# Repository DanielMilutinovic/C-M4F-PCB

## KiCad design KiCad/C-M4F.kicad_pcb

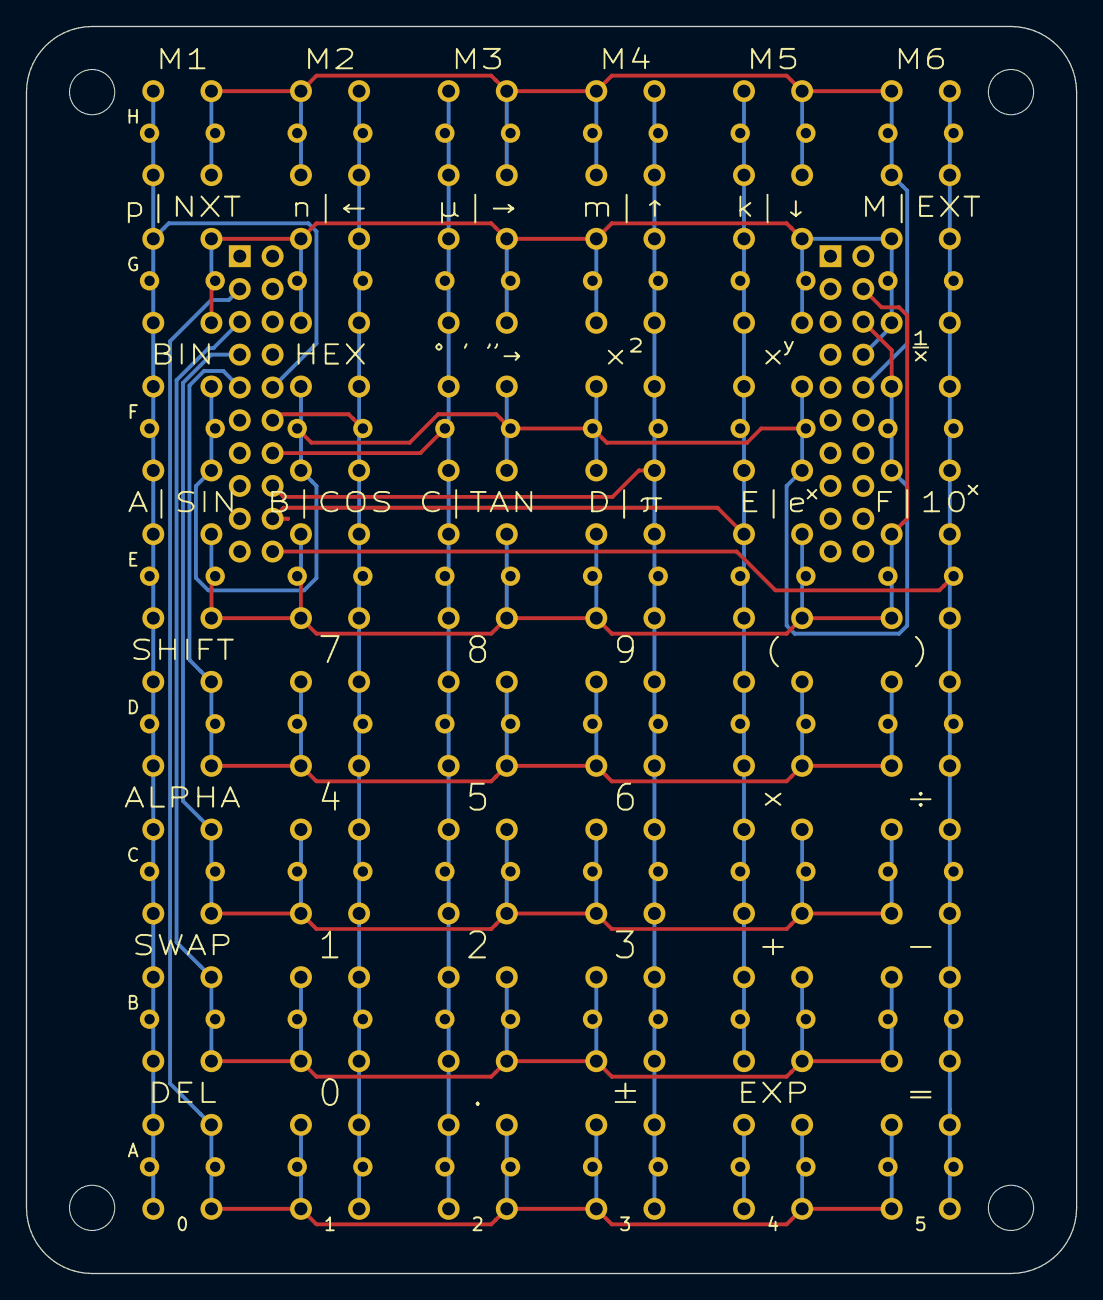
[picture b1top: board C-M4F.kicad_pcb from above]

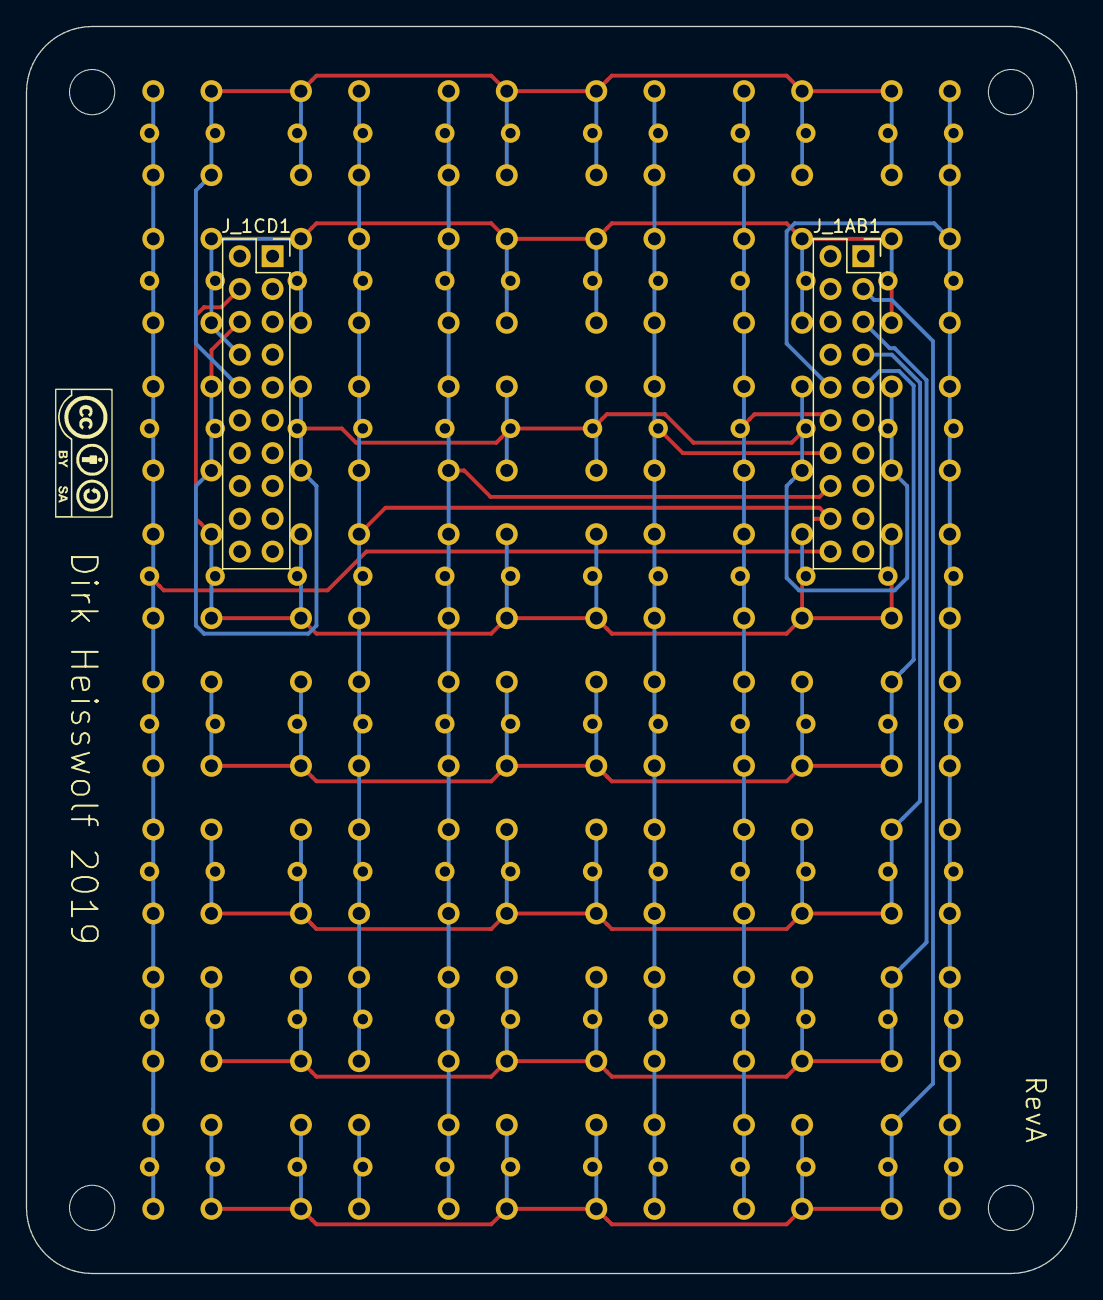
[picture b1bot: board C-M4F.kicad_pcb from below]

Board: 2 copper layers, 81.3 x 96.5 mm, 50 parts (2 on the bottom side), 15 nets.

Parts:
J_1AB1: BoosterPackXL_AB
J_1CD1: BoosterPackXL_CD
KEY_A0, KEY_A1, KEY_A2, KEY_A3, KEY_A4, KEY_A5: KEY; key
KEY_B0, KEY_B1, KEY_B2, KEY_B3, KEY_B4, KEY_B5: KEY; key
KEY_C0, KEY_C1, KEY_C2, KEY_C3, KEY_C4, KEY_C5: KEY; key
KEY_D0, KEY_D1, KEY_D2, KEY_D3, KEY_D4, KEY_D5: KEY; key
KEY_E0, KEY_E1, KEY_E2, KEY_E3, KEY_E4, KEY_E5: KEY; key
KEY_F0, KEY_F1, KEY_F2, KEY_F3, KEY_F4, KEY_F5: KEY; key
KEY_G0, KEY_G1, KEY_G2, KEY_G3, KEY_G4, KEY_G5: KEY; key
KEY_H0, KEY_H1, KEY_H2, KEY_H3, KEY_H4, KEY_H5: KEY; key

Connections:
GND: J_1AB1.B2, J_1CD1.D1
KEY_COLUMN_0: J_1AB1.B5, KEY_A0.2, KEY_A0.4, KEY_A0.6, KEY_B0.2, KEY_B0.4, KEY_B0.6, KEY_C0.2, KEY_C0.4, KEY_C0.6, KEY_D0.2, KEY_D0.4, KEY_D0.6, KEY_E0.2, KEY_E0.4, KEY_E0.6, KEY_F0.2, KEY_F0.4, KEY_F0.6, KEY_G0.2, KEY_G0.4, KEY_G0.6, KEY_H0.2, KEY_H0.4, KEY_H0.6
KEY_COLUMN_1: J_1AB1.B6, KEY_A1.2, KEY_A1.4, KEY_A1.6, KEY_B1.2, KEY_B1.4, KEY_B1.6, KEY_C1.2, KEY_C1.4, KEY_C1.6, KEY_D1.2, KEY_D1.4, KEY_D1.6, KEY_E1.2, KEY_E1.4, KEY_E1.6, KEY_F1.2, KEY_F1.4, KEY_F1.6, KEY_G1.2, KEY_G1.4, KEY_G1.6, KEY_H1.2, KEY_H1.4, KEY_H1.6
KEY_COLUMN_2: J_1AB1.B7, KEY_A2.2, KEY_A2.4, KEY_A2.6, KEY_B2.2, KEY_B2.4, KEY_B2.6, KEY_C2.2, KEY_C2.4, KEY_C2.6, KEY_D2.2, KEY_D2.4, KEY_D2.6, KEY_E2.2, KEY_E2.4, KEY_E2.6, KEY_F2.2, KEY_F2.4, KEY_F2.6, KEY_G2.2, KEY_G2.4, KEY_G2.6, KEY_H2.2, KEY_H2.4, KEY_H2.6
KEY_COLUMN_3: J_1AB1.B8, KEY_A3.2, KEY_A3.4, KEY_A3.6, KEY_B3.2, KEY_B3.4, KEY_B3.6, KEY_C3.2, KEY_C3.4, KEY_C3.6, KEY_D3.2, KEY_D3.4, KEY_D3.6, KEY_E3.2, KEY_E3.4, KEY_E3.6, KEY_F3.2, KEY_F3.4, KEY_F3.6, KEY_G3.2, KEY_G3.4, KEY_G3.6, KEY_H3.2, KEY_H3.4, KEY_H3.6
KEY_COLUMN_4: J_1AB1.B9, KEY_A4.2, KEY_A4.4, KEY_A4.6, KEY_B4.2, KEY_B4.4, KEY_B4.6, KEY_C4.2, KEY_C4.4, KEY_C4.6, KEY_D4.2, KEY_D4.4, KEY_D4.6, KEY_E4.2, KEY_E4.4, KEY_E4.6, KEY_F4.2, KEY_F4.4, KEY_F4.6, KEY_G4.2, KEY_G4.4, KEY_G4.6, KEY_H4.2, KEY_H4.4, KEY_H4.6
KEY_COLUMN_5: J_1AB1.B10, KEY_A5.2, KEY_A5.4, KEY_A5.6, KEY_B5.2, KEY_B5.4, KEY_B5.6, KEY_C5.2, KEY_C5.4, KEY_C5.6, KEY_D5.2, KEY_D5.4, KEY_D5.6, KEY_E5.2, KEY_E5.4, KEY_E5.6, KEY_F5.2, KEY_F5.4, KEY_F5.6, KEY_G5.2, KEY_G5.4, KEY_G5.6, KEY_H5.2, KEY_H5.4, KEY_H5.6
KEY_ROW_A: J_1AB1.A2, KEY_A0.1, KEY_A0.3, KEY_A0.5, KEY_A1.1, KEY_A1.3, KEY_A1.5, KEY_A2.1, KEY_A2.3, KEY_A2.5, KEY_A3.1, KEY_A3.3, KEY_A3.5, KEY_A4.1, KEY_A4.3, KEY_A4.5, KEY_A5.1, KEY_A5.3, KEY_A5.5
KEY_ROW_B: J_1AB1.A3, KEY_B0.1, KEY_B0.3, KEY_B0.5, KEY_B1.1, KEY_B1.3, KEY_B1.5, KEY_B2.1, KEY_B2.3, KEY_B2.5, KEY_B3.1, KEY_B3.3, KEY_B3.5, KEY_B4.1, KEY_B4.3, KEY_B4.5, KEY_B5.1, KEY_B5.3, KEY_B5.5
KEY_ROW_C: J_1AB1.A4, KEY_C0.1, KEY_C0.3, KEY_C0.5, KEY_C1.1, KEY_C1.3, KEY_C1.5, KEY_C2.1, KEY_C2.3, KEY_C2.5, KEY_C3.1, KEY_C3.3, KEY_C3.5, KEY_C4.1, KEY_C4.3, KEY_C4.5, KEY_C5.1, KEY_C5.3, KEY_C5.5
KEY_ROW_D: J_1AB1.A5, KEY_D0.1, KEY_D0.3, KEY_D0.5, KEY_D1.1, KEY_D1.3, KEY_D1.5, KEY_D2.1, KEY_D2.3, KEY_D2.5, KEY_D3.1, KEY_D3.3, KEY_D3.5, KEY_D4.1, KEY_D4.3, KEY_D4.5, KEY_D5.1, KEY_D5.3, KEY_D5.5
KEY_ROW_E: J_1CD1.D2, KEY_E0.1, KEY_E0.3, KEY_E0.5, KEY_E1.1, KEY_E1.3, KEY_E1.5, KEY_E2.1, KEY_E2.3, KEY_E2.5, KEY_E3.1, KEY_E3.3, KEY_E3.5, KEY_E4.1, KEY_E4.3, KEY_E4.5, KEY_E5.1, KEY_E5.3, KEY_E5.5
KEY_ROW_F: J_1CD1.D3, KEY_F0.1, KEY_F0.3, KEY_F0.5, KEY_F1.1, KEY_F1.3, KEY_F1.5, KEY_F2.1, KEY_F2.3, KEY_F2.5, KEY_F3.1, KEY_F3.3, KEY_F3.5, KEY_F4.1, KEY_F4.3, KEY_F4.5, KEY_F5.1, KEY_F5.3, KEY_F5.5
KEY_ROW_G: J_1CD1.D4, KEY_G0.1, KEY_G0.3, KEY_G0.5, KEY_G1.1, KEY_G1.3, KEY_G1.5, KEY_G2.1, KEY_G2.3, KEY_G2.5, KEY_G3.1, KEY_G3.3, KEY_G3.5, KEY_G4.1, KEY_G4.3, KEY_G4.5, KEY_G5.1, KEY_G5.3, KEY_G5.5
KEY_ROW_H: J_1CD1.D5, KEY_H0.1, KEY_H0.3, KEY_H0.5, KEY_H1.1, KEY_H1.3, KEY_H1.5, KEY_H2.1, KEY_H2.3, KEY_H2.5, KEY_H3.1, KEY_H3.3, KEY_H3.5, KEY_H4.1, KEY_H4.3, KEY_H4.5, KEY_H5.1, KEY_H5.3, KEY_H5.5

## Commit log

2019-08-09 work in progress
2019-08-09 first schematic proposal
2019-10-05 initial PCB layout
2019-10-05 cleanup
2019-10-05 updated schemactics
2019-12-03 Set theme jekyll-theme-cayman
